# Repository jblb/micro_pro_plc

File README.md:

### A 4 inputs 4 outputs PLC board based on [Arduino micro pro] (or clone) to drive a 4 Way [relay board] and made to run with [open_PLC]

### Status:

work in progress...

__Micro pro PLC__ is a  small _Programable Logic Controlor_ board based on [Arduino micro pro] (ATmega32U4 microcontroler).
It is designed for small systems with 4 digital inputs, 4 digital outputs, 2 analog inputs and a Modbus/RS485 access.
It is designed to fit on easy available 4 way [relay board]

I first designed it for use with [open_PLC] but it can be use with Arduino IDE or any other way you want to devellop the software you put on the controler

### Simulated 3D view

### Connection diagram

### Arduino pins used

| Board pin | Arduino pin |
| :-------- | :-----------|
| I0.0 | D2 |
| I0.1 | D3 |
| I0.2 | D4 |
| I0.3 | D5 |
| Output0 | D7 |
| Output1 | D8 |
| Output2 | D14 |
| Output3 | D15 |
| IW0.0 | A0 |
| IW0.1 | A1 |

- Modbus/RS485 drived by D1 for Tx and D0 for RX (Serial1)
- RS485 is enabled by D6
- Outputs open drain - 200mA drain output
- Input actived by pooling to GND (need to drain ~20mA)

### Schematic

PDF version available [here](./Docs/pro_micro_plc_sch.pdf)

### BOM
|Reference |Value |Footprint|
|:---------|:-----|:--------|
|C1,C2,C3  |100nF |SMD 0805 |
|D1,D2,D3,D4 |LED_3mm ||
|J1 |01x06_Pin |PinSocket_2.54mm |
|J2,J3,J4 ||TerminalBlock_Phoenix_MKDS 5.00mm |
|J5 |01x02_Pin |PinHeader_2.54mm |
|J6,J7 |01x04_Pin |PinHeader_2.54mm or JST HX|
|Q1,Q2,Q3,Q4 |2N7002K |SOT-23 |
|R1,R2,R3,R4 |10k |SMD 0805 |
|R5,R6,R7,R8 |4k7 |SMD 0805 |
|R9 |120 |SMD 0805 |
|R10,R11,R12,R13 |100 |SMD 0805 |
|R14,R15 |20k |SMD 0805 |
|U1 |Sparkfun_Pro_Micro or Clone|
|U2,U3,U4,U5 |PC817 |DIP4 |
|U6 |MAX485E |DIP8 |

also available [here](./Docs/pro_micro_plc_BOM.md)

[open_PLC]: https://autonomylogic.com/
[Arduino micro pro]: https://www.sparkfun.com/products/12640
[relay board]: https://fr.aliexpress.com/item/1005002867727977.html

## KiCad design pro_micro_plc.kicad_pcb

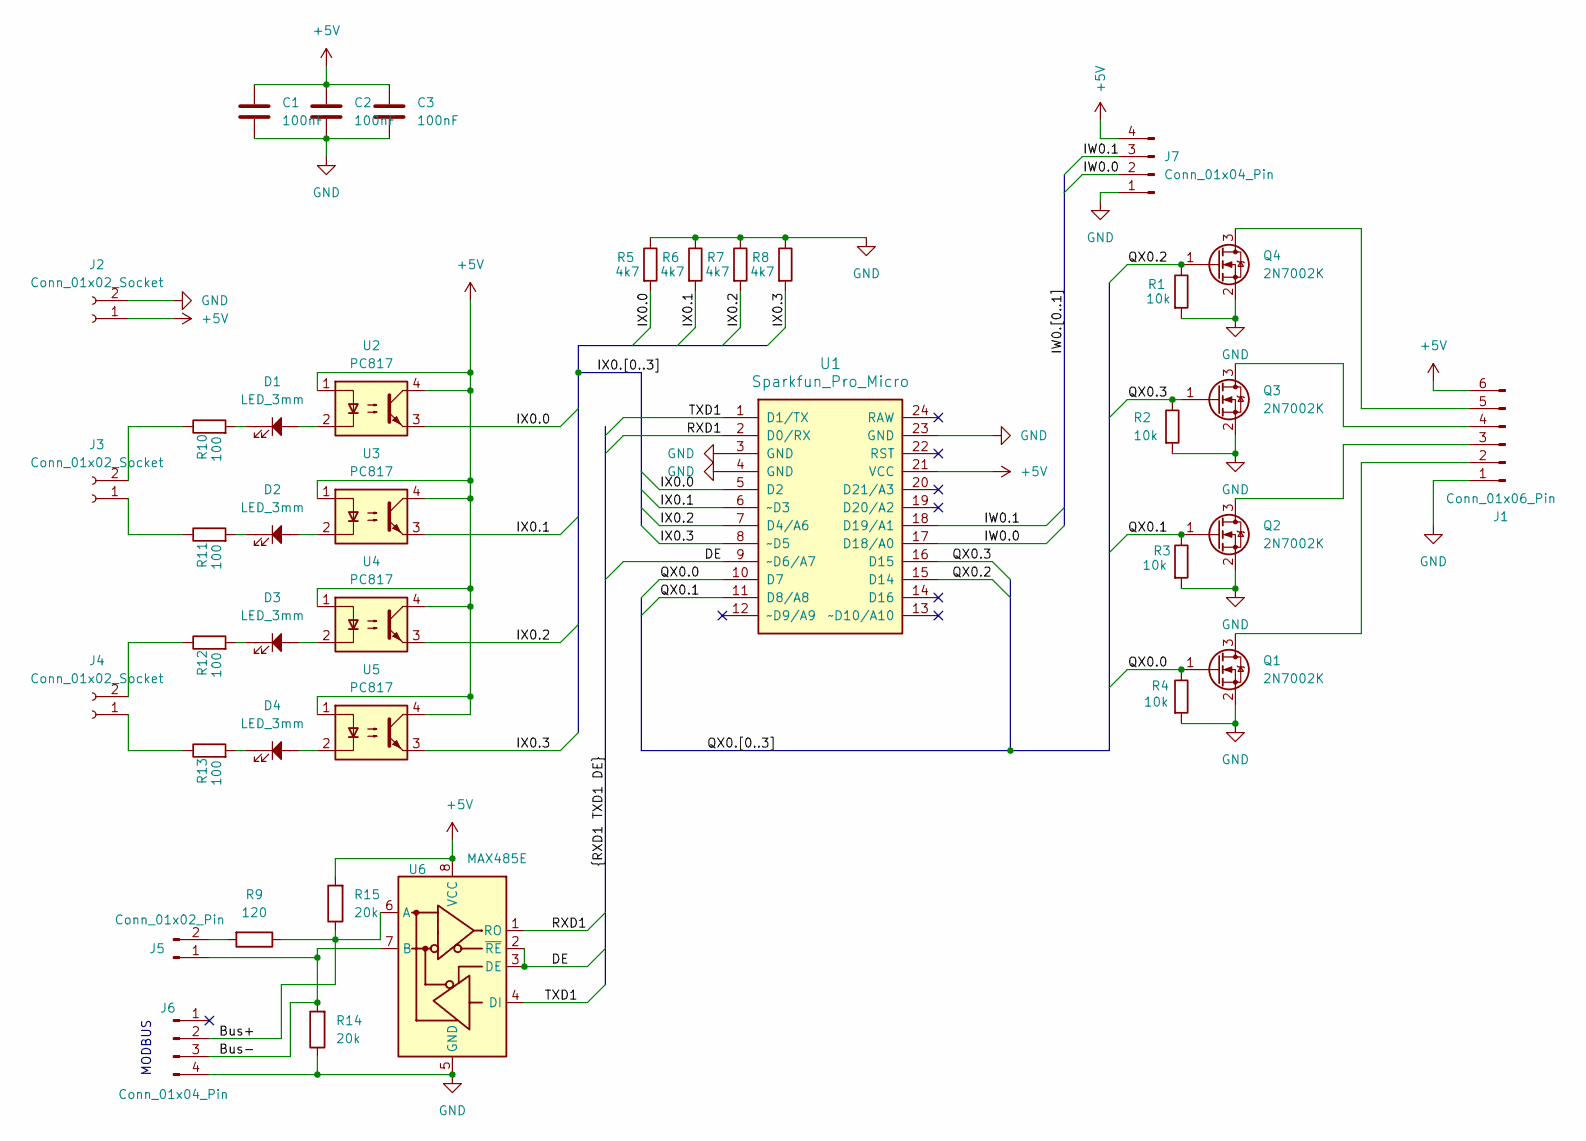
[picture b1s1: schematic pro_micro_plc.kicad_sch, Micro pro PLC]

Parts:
C1, C2, C3: 100nF; C_0805_2012Metric_Pad1.18x1.45mm_HandSolder
D1, D2, D3, D4: LED_3mm; LED_D3.0mm
J1: Conn_01x06_Pin; PinSocket_1x06_P2.54mm_Vertical
J2, J3, J4: Conn_01x02_Socket; TerminalBlock_Phoenix_MKDS-1,5-2_1x02_P5.00mm_Horizontal
J5: Conn_01x02_Pin; PinHeader_1x02_P2.54mm_Vertical
J6, J7: Conn_01x04_Pin; PinHeader_1x04_P2.54mm_Vertical
Q1, Q2, Q3, Q4: 2N7002K; SOT-23_Handsoldering
R1, R2, R3, R4: 10k; R_0805_2012Metric_Pad1.20x1.40mm_HandSolder
R5, R6, R7, R8: 4k7; R_0805_2012Metric_Pad1.20x1.40mm_HandSolder
R9: 120; R_0805_2012Metric_Pad1.20x1.40mm_HandSolder
R10, R11, R12, R13: 100; R_0805_2012Metric_Pad1.20x1.40mm_HandSolder
R14, R15: 20k; R_0805_2012Metric_Pad1.20x1.40mm_HandSolder
U1: Sparkfun_Pro_Micro
U2, U3, U4, U5: PC817; DIP-4_W7.62mm
U6: MAX485E; DIP-8_W7.62mm

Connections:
+5V: C1.1, C2.1, C3.1, J1.6, J2.1, J7.4, R15.2, U1.21 (VCC), U2.1, U2.4, U3.1, U3.4, U4.1, U4.4, U5.1, U5.4, U6.8 (VCC)
/Bus+: J6.2, R9.1, R15.1, U6.6 (A)
/Bus-: J5.1, J6.3, R14.2, U6.7 (B)
/DE: U1.9 (~D6/A7), U6.2 (~RE), U6.3 (DE)
/IW0.0: J7.2, U1.17 (D18/A0)
/IW0.1: J7.3, U1.18 (D19/A1)
/IX0.0: R5.1, U1.5 (D2), U2.3
/IX0.1: R6.1, U1.6 (~D3), U3.3
/IX0.2: R7.1, U1.7 (D4/A6), U4.3
/IX0.3: R8.1, U1.8 (~D5), U5.3
/QX0.0: Q1.1 (G), R4.2, U1.10 (D7)
/QX0.1: Q2.1 (G), R3.2, U1.11 (D8/A8)
/QX0.2: Q4.1 (G), R1.2, U1.15 (D14)
/QX0.3: Q3.1 (G), R2.2, U1.16 (D15)
/RXD1: U1.2 (D0/RX), U6.1 (RO)
/TXD1: U1.1 (D1/TX), U6.4 (DI)
GND: C1.2, C2.2, C3.2, J1.1, J2.2, J6.4, J7.1, Q1.2 (S), Q2.2 (S), Q3.2 (S), Q4.2 (S), R1.1, R2.1, R3.1, R4.1, R5.2, R6.2, R7.2, R8.2, R14.1, U1.3 (GND), U1.4 (GND), U1.23 (GND), U6.5 (GND)
unnamed: D1.1, R10.1
unnamed: D1.2, U2.2
unnamed: D2.1, R11.1
unnamed: D2.2, U3.2
unnamed: D3.1, R12.1
unnamed: D3.2, U4.2
unnamed: D4.1, R13.1
unnamed: D4.2, U5.2
unnamed: J1.2, Q1.3 (D)
unnamed: J1.3, Q2.3 (D)
unnamed: J1.4, Q3.3 (D)
unnamed: J1.5, Q4.3 (D)
unnamed: J3.1, R11.2
unnamed: J3.2, R10.2
unnamed: J4.1, R13.2
unnamed: J4.2, R12.2
unnamed: J5.2, R9.2

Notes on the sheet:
MODBUS

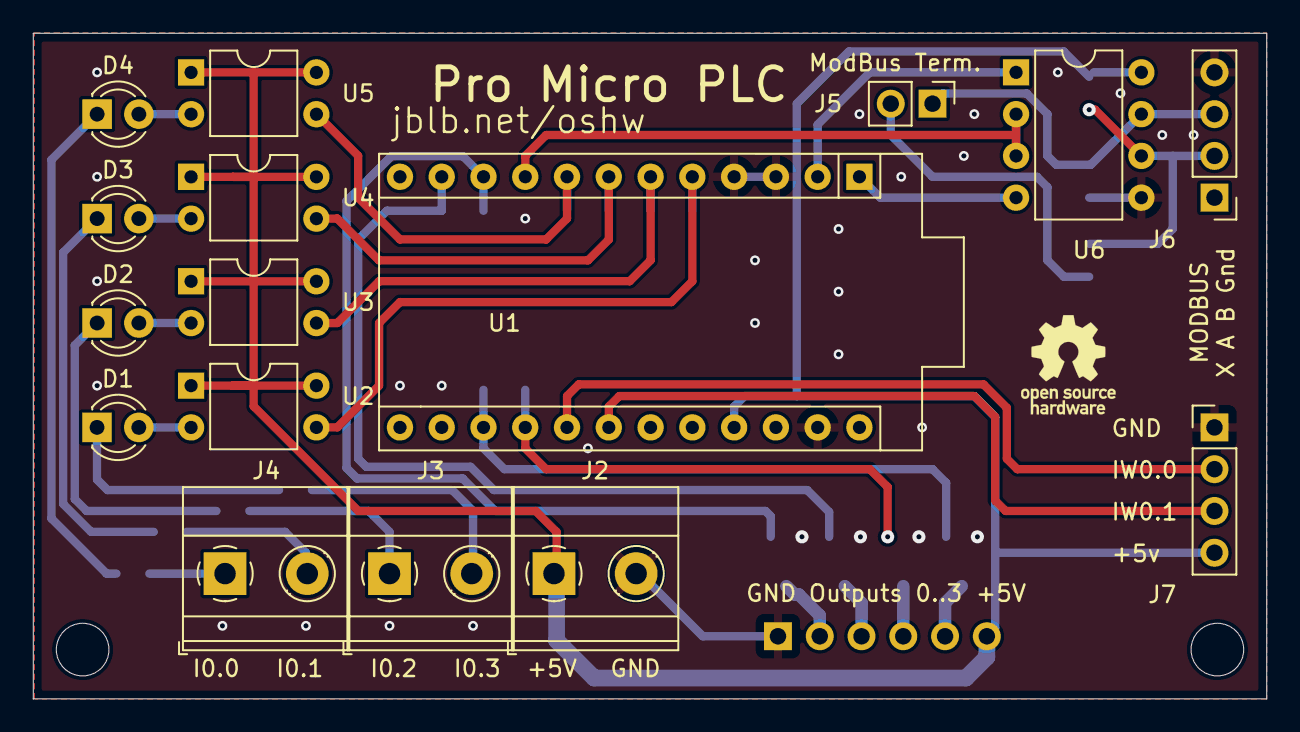
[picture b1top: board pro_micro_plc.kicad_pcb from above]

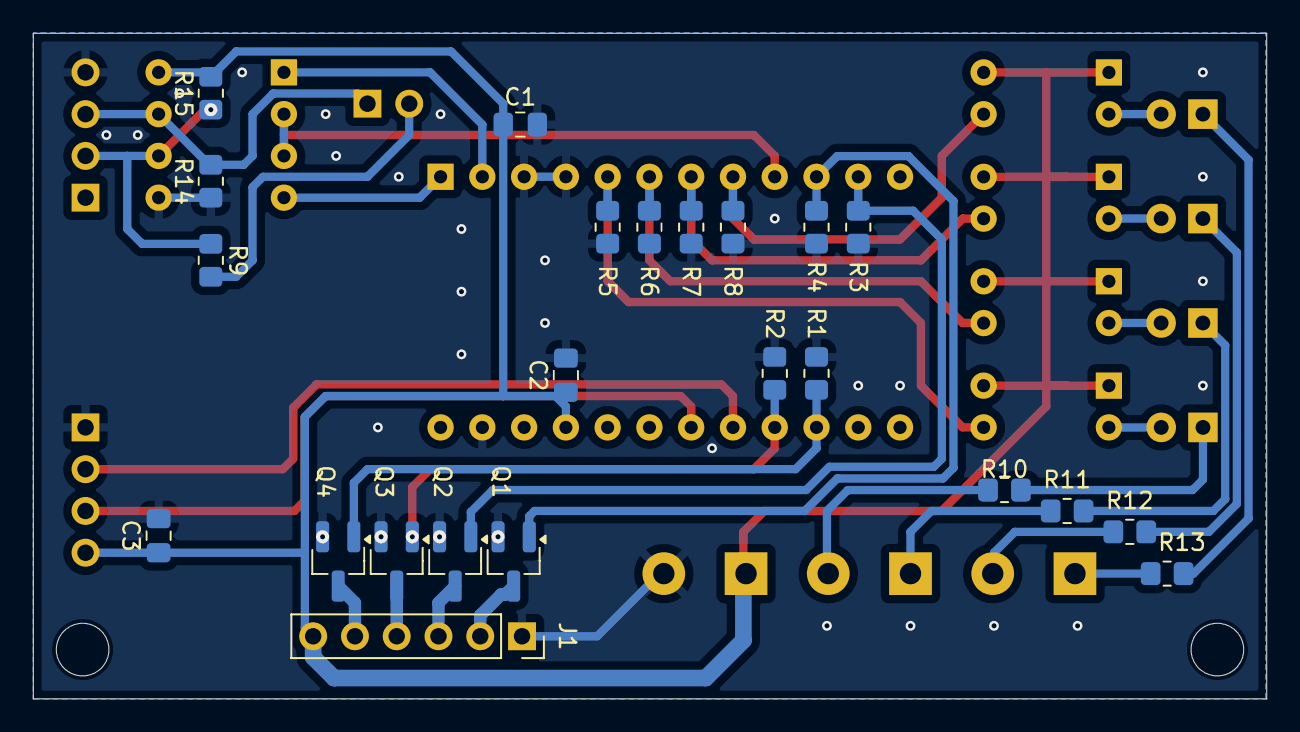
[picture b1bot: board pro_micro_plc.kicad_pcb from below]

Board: 2 copper layers, 75.0 x 40.5 mm, 39 parts (23 on the bottom side), 34 nets.

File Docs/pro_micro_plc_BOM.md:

|Reference |Value |Footprint|
|:---------|:-----|:--------|
|C1,C2,C3  |100nF |SMD 0805 |
|D1,D2,D3,D4 |LED_3mm ||
|J1 |01x06_Pin |PinSocket_2.54mm |
|J2,J3,J4 ||TerminalBlock_Phoenix_MKDS 5.00mm |
|J5 |01x02_Pin |PinHeader_2.54mm |
|J6,J7 |01x04_Pin |PinHeader_2.54mm |
|Q1,Q2,Q3,Q4 |2N7002K |SOT-23 |
|R1,R2,R3,R4 |10k |SMD 0805 |
|R5,R6,R7,R8 |4k7 |SMD 0805 |
|R9 |120 |SMD 0805 |
|R10,R11,R12,R13 |100 |SMD 0805 |
|R14,R15 |20k |SMD 0805 |
|U1 |Sparkfun_Pro_Micro |
|U2,U3,U4,U5 |PC817 |DIP4 |
|U6 |MAX485E |DIP8 |

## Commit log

2024-08-25 initial board stuff
2024-08-25 ajust gitignore
2024-08-25 rename reps
2024-08-25 add analog input
2024-08-26 smallest PCB
2024-08-28 more space for max485 and vias on ground
2024-09-02 smalls improvments
2024-09-06 update terminal blocks
